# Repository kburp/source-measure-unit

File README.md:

# Source Measure Unit
Schematic, layout, and firmware files for 12V/65mA source measure unit project.

Schematic and layout were created using KiCAD. Firmware for the RP2040 microcontroller was written using the Arduino IDE and the Arduino-Pico project.

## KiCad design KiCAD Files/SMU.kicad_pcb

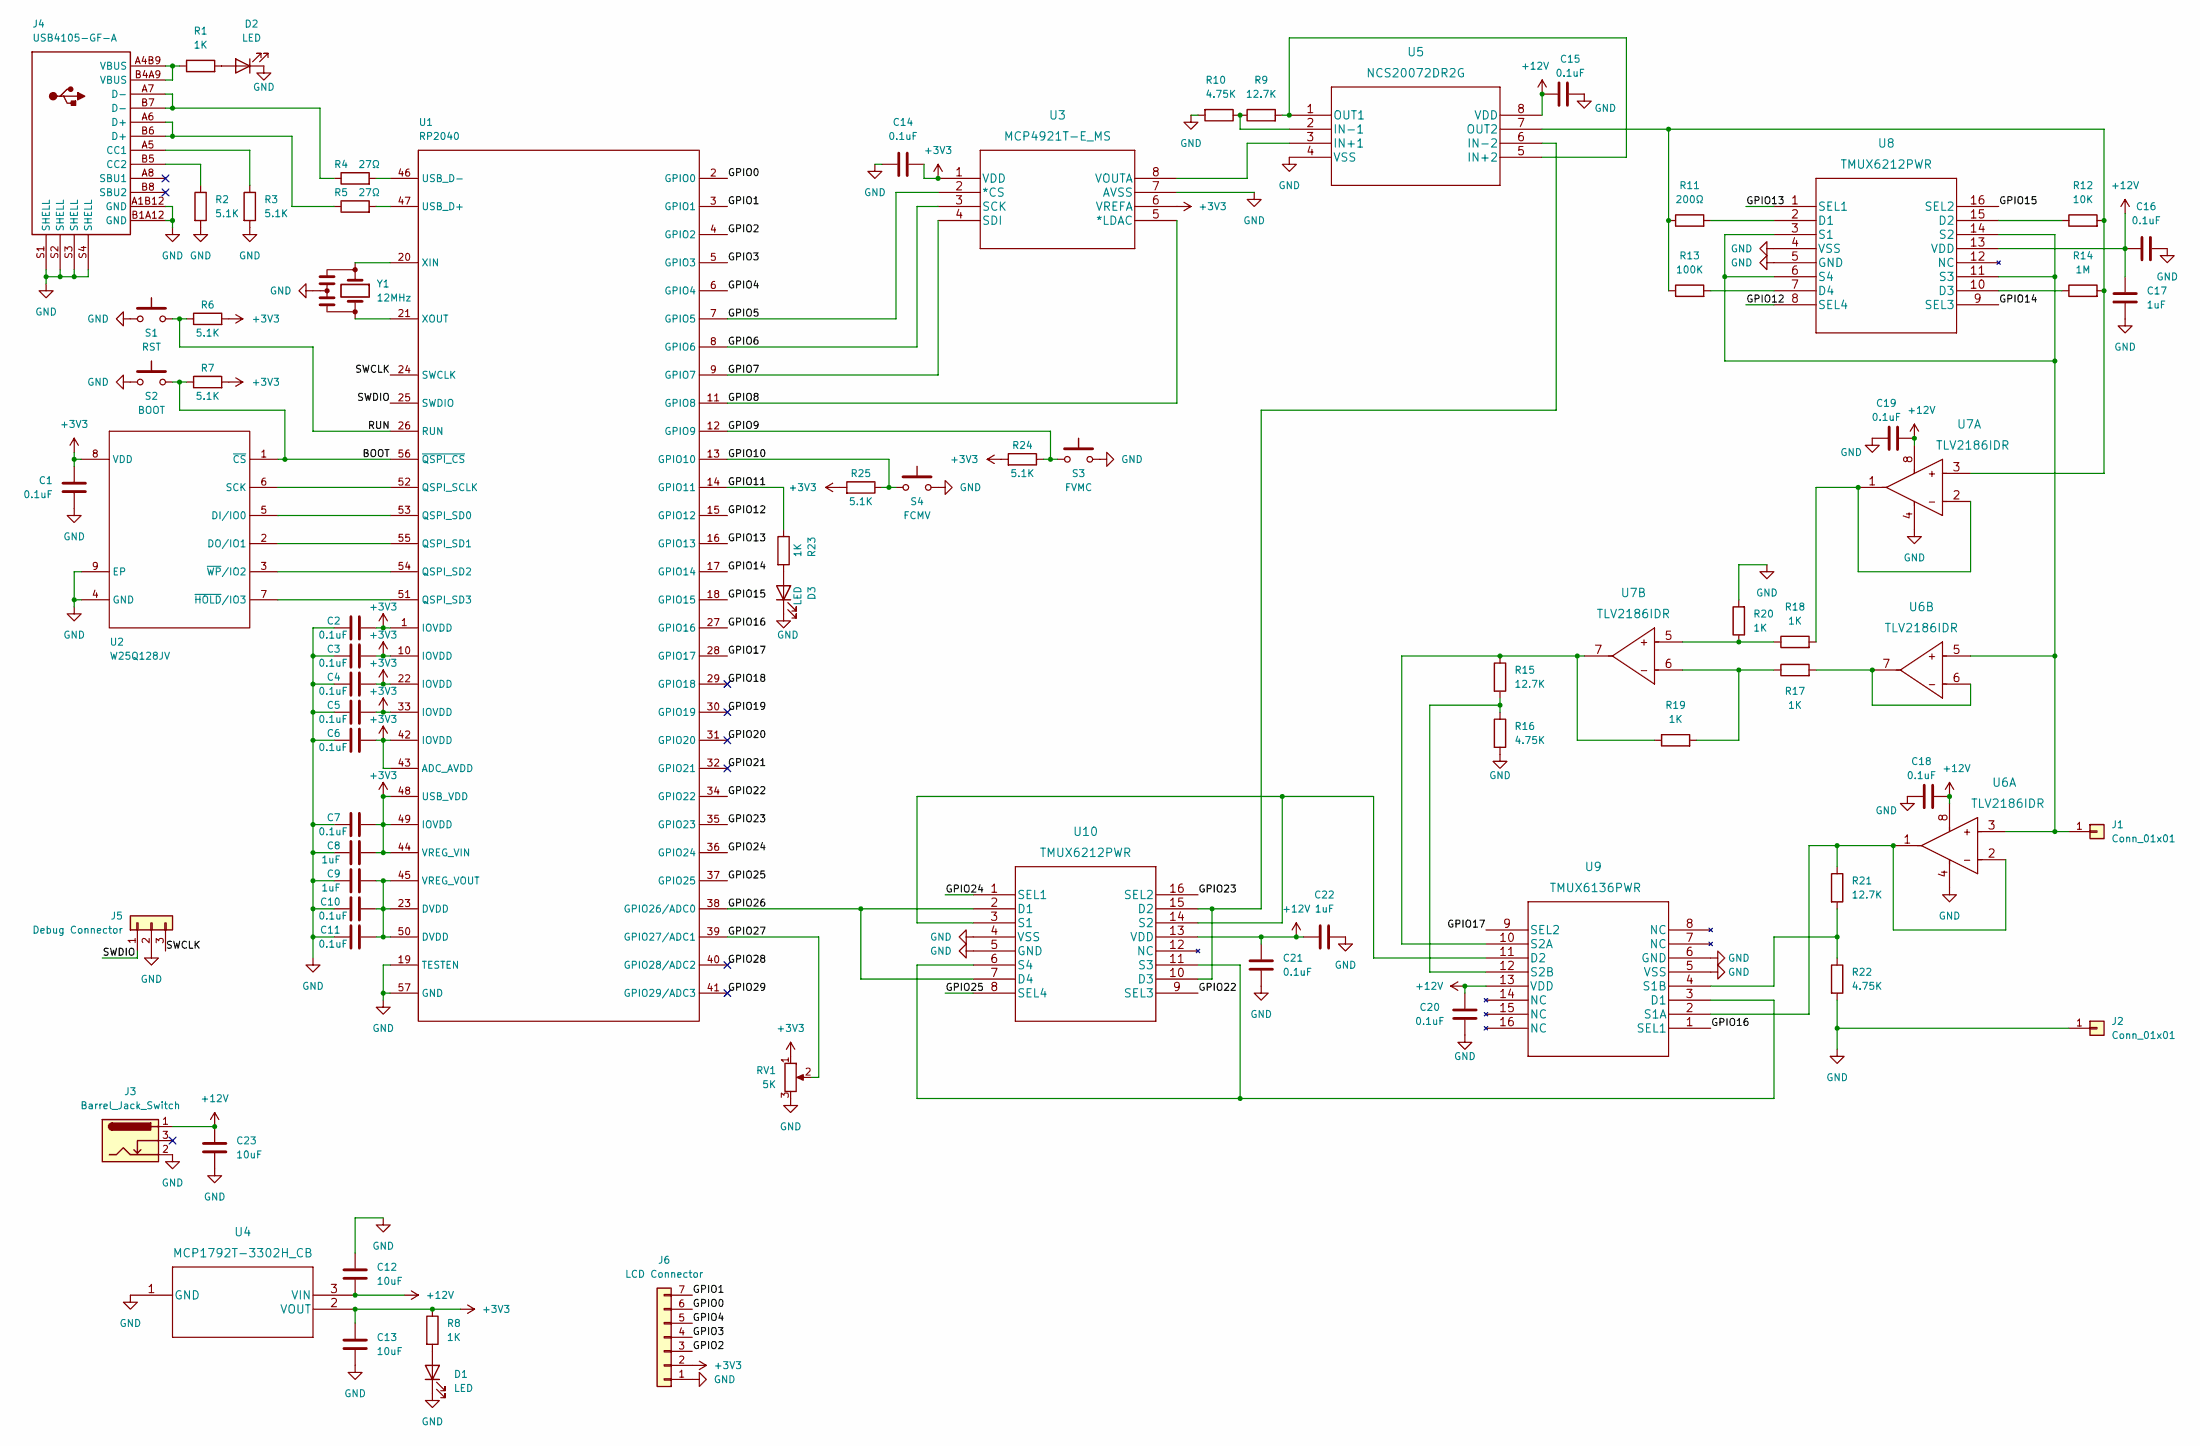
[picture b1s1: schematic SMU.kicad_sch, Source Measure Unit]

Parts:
C1, C2, C3, C4, C5, C6, C7, C10, C11, C14, C15, C16, C18, C19, C20, C21: 0.1uF; C_0603_1608Metric
C8, C9, C17, C22: 1uF; C_0603_1608Metric
C12, C13, C23: 10uF; C_0603_1608Metric
D1, D2, D3: LED; LED_0805_2012Metric
J1, J2: Conn_01x01; PinHeader_1x01_P2.54mm_Vertical
J3: Barrel_Jack_Switch; CUI_PJ-202B
J4: USB4105-GF-A
J5: Debug Connector; PinHeader_1x03_P2.54mm_Vertical
J6: LCD Connector; PinHeader_1x07_P2.54mm_Vertical
R1, R8, R17, R18, R19, R20, R23: 1K; R_0603_1608Metric
R2, R3, R6, R7, R24, R25: 5.1K; R_0603_1608Metric
R4, R5: 27Ω; R_0603_1608Metric
R9, R15, R21: 12.7K; R_0603_1608Metric
R10, R16, R22: 4.75K; R_0603_1608Metric
R11: 200Ω; R_0603_1608Metric
R12: 10K; R_0603_1608Metric
R13: 100K; R_0603_1608Metric
R14: 1M; R_0603_1608Metric
RV1: 5K; TRIM_3352T-1-502LF
S1: RST; TL3301AFxxxxJ
S2: BOOT; TL3301AFxxxxJ
S3: FVMC; TL3301AFxxxxJ
S4: FCMV; TL3301AFxxxxJ
U1: RP2040
U2: W25Q128JV; WSON-8-1EP_6x5mm_P1.27mm_EP3.4x4.3mm
U3: MCP4921T-E_MS; MCP4921T-E&slash_MS
U4: MCP1792T-3302H_CB; MCP1792T-3302H&slash_CB
U5: NCS20072DR2G
U6, U7: TLV2186IDR
U8, U10: TMUX6212PWR
U9: TMUX6136PWR
Y1: 12MHz; CSTNE

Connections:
+3V3: C1.2, C2.1, C3.1, C4.1, C5.1, C6.1, C7.1, C8.1, C13.1, C14.2, J6.2, R6.2, R7.2, R8.1, R24.2, R25.2, RV1.1, U1.1 (IOVDD), U1.10 (IOVDD), U1.22 (IOVDD), U1.33 (IOVDD), U1.42 (IOVDD), U1.43 (ADC_AVDD), U1.44 (VREG_VIN), U1.48 (USB_VDD), U1.49 (IOVDD), U2.8 (VDD), U3.1 (VDD), U3.6 (VREFA), U4.2 (VOUT)
+12V: C12.1, C15.2, C16.1, C17.1, C18.2, C19.2, C20.2, C21.1, C22.1, C23.1, J3.1, U4.3 (VIN), U5.8 (VDD), U6.8 (V+), U7.8 (V+), U8.13 (VDD), U9.13 (VDD), U10.13 (VDD)
/BOOT: R7.1, S2.2, U1.56 (~QSPI_CS), U2.1 (~CS)
/GPIO0: J6.6, U1.2 (GPIO0)
/GPIO1: J6.7, U1.3 (GPIO1)
/GPIO2: J6.3, U1.4 (GPIO2)
/GPIO3: J6.4, U1.5 (GPIO3)
/GPIO4: J6.5, U1.6 (GPIO4)
/GPIO5: U1.7 (GPIO5), U3.2 (*CS)
/GPIO6: U1.8 (GPIO6), U3.3 (SCK)
/GPIO7: U1.9 (GPIO7), U3.4 (SDI)
/GPIO8: U1.11 (GPIO8), U3.5 (*LDAC)
/GPIO9: R24.1, S3.2, U1.12 (GPIO9)
/GPIO10: R25.1, S4.2, U1.13 (GPIO10)
/GPIO11: R23.1, U1.14 (GPIO11)
/GPIO12: U1.15 (GPIO12), U8.8 (SEL4)
/GPIO13: U1.16 (GPIO13), U8.1 (SEL1)
/GPIO14: U1.17 (GPIO14), U8.9 (SEL3)
/GPIO15: U1.18 (GPIO15), U8.16 (SEL2)
/GPIO16: U1.27 (GPIO16), U9.1 (SEL1)
/GPIO17: U1.28 (GPIO17), U9.9 (SEL2)
/GPIO18: U1.29 (GPIO18)
/GPIO19: U1.30 (GPIO19)
/GPIO20: U1.31 (GPIO20)
/GPIO21: U1.32 (GPIO21)
/GPIO22: U1.34 (GPIO22), U10.9 (SEL3)
/GPIO23: U1.35 (GPIO23), U10.16 (SEL2)
/GPIO24: U1.36 (GPIO24), U10.1 (SEL1)
/GPIO25: U1.37 (GPIO25), U10.8 (SEL4)
/GPIO26: U1.38 (GPIO26/ADC0), U10.2 (D1), U10.7 (D4)
/GPIO27: RV1.2, U1.39 (GPIO27/ADC1)
/GPIO28: U1.40 (GPIO28/ADC2)
/GPIO29: U1.41 (GPIO29/ADC3)
/RUN: R6.1, S1.2, U1.26 (RUN)
/SWCLK: J5.3, U1.24 (SWCLK)
/SWDIO: J5.1, U1.25 (SWDIO)
GND: C1.1, C2.2, C3.2, C4.2, C5.2, C6.2, C7.2, C8.2, C9.2, C10.2, C11.2, C12.2, C13.2, C14.1, C15.1, C16.2, C17.2, C18.1, C19.1, C20.1, C21.2, C22.2, C23.2, D1.1 (K), D2.1 (K), D3.1 (K), J2.1, J3.2, J4.A1B12 (GND), J4.B1A12 (GND), J4.S1 (SHELL), J4.S2 (SHELL), J4.S3 (SHELL), J4.S4 (SHELL), J5.2, J6.1, R2.2, R3.2, R10.2, R16.2, R20.2, R22.2, RV1.3, S1.1, S2.1, S3.1, S4.1, U1.19 (TESTEN), U1.57 (GND), U2.4 (GND), U2.9 (EP), U3.7 (AVSS), U4.1 (GND), U5.4 (VSS), U6.4 (V-), U7.4 (V-), U8.4 (VSS), U8.5 (GND), U9.5 (VSS), U9.6 (GND), U10.4 (VSS), U10.5 (GND), Y1.2
unnamed: C9.1, C10.1, C11.1, U1.23 (DVDD), U1.45 (VREG_VOUT), U1.50 (DVDD)
unnamed: D1.2 (A), R8.2
unnamed: D2.2 (A), R1.2
unnamed: D3.2 (A), R23.2
unnamed: J1.1, U6.3 (+IN_A), U6.5 (+IN_B), U8.3 (S1), U8.6 (S4), U8.11 (S3), U8.14 (S2)
unnamed: J4.A4B9 (VBUS), J4.B4A9 (VBUS), R1.1
unnamed: J4.A5 (CC1), R3.1
unnamed: J4.A6 (D+), J4.B6 (D+), R5.1
unnamed: J4.A7 (D-), J4.B7 (D-), R4.1
unnamed: J4.B5 (CC2), R2.1
unnamed: R4.2, U1.46 (USB_D-)
unnamed: R5.2, U1.47 (USB_D+)
unnamed: R9.2, U5.1 (OUT1), U5.5 (IN+2)
unnamed: R9.1, R10.1, U5.2 (IN-1)
unnamed: R11.1, R12.2, R13.1, R14.2, U5.7 (OUT2), U7.3 (+IN_A)
unnamed: R11.2, U8.2 (D1)
unnamed: R12.1, U8.15 (D2)
unnamed: R13.2, U8.7 (D4)
unnamed: R14.1, U8.10 (D3)
unnamed: R15.1, R19.1, U7.7 (OUT_B), U9.10 (S2A)
unnamed: R15.2, R16.1, U9.12 (S2B)
unnamed: R17.1, R19.2, U7.6 (-IN_B)
unnamed: R17.2, U6.6 (-IN_B), U6.7 (OUT_B)
unnamed: R18.1, R20.1, U7.5 (+IN_B)
unnamed: R18.2, U7.1 (OUT_A), U7.2 (-IN_A)
unnamed: R21.1, U6.1 (OUT_A), U6.2 (-IN_A), U9.2 (S1A)
unnamed: R21.2, R22.1, U9.4 (S1B)
unnamed: U1.20 (XIN), Y1.1
unnamed: U1.21 (XOUT), Y1.3
unnamed: U1.51 (QSPI_SD3), U2.7 (~HOLD/IO3)
unnamed: U1.52 (QSPI_SCLK), U2.6 (SCK)
unnamed: U1.53 (QSPI_SD0), U2.5 (DI/IO0)
unnamed: U1.54 (QSPI_SD2), U2.3 (~WP/IO2)
unnamed: U1.55 (QSPI_SD1), U2.2 (DO/IO1)
unnamed: U3.8 (VOUTA), U5.3 (IN+1)
unnamed: U5.6 (IN-2), U10.10 (D3), U10.15 (D2)
unnamed: U9.3 (D1), U10.6 (S4), U10.11 (S3)
unnamed: U9.11 (D2), U10.3 (S1), U10.14 (S2)

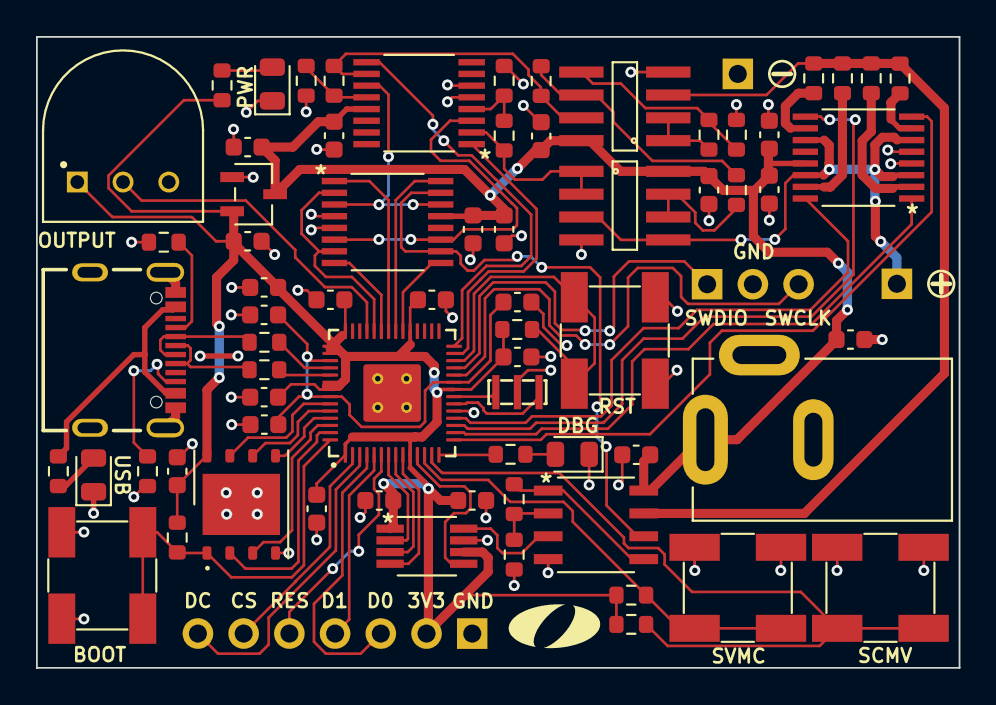
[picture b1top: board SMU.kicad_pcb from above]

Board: 2 copper layers, 51.3 x 35.1 mm, 74 parts (0 on the bottom side), 69 nets.

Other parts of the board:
OlinLogoSm: G***; OlinLogoSm

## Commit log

2022-12-01 Added KiCAD files
2022-12-01 First iteration of DAC firmware
2022-12-01 Remove BOM
2022-12-01 Add to DAC code
2022-12-02 Completed DAC code
2022-12-03 Define all GPIO pins
2022-12-03 Separate DAC configuration into helper function
2022-12-04 Set up source voltage measure current
2022-12-04 Fixed logic of source voltage measure current
2022-12-09 Finish SPI testing
2022-12-13 Implement both SMU modes
2022-12-16 Complete SMU implementation

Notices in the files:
parts and their libraries:
Copyright 2021 Accelerated Designs. All rights reserved.
